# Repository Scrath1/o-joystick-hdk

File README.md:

# What is this?
This repository is a fork from olukelo's gimbal repository in which I uploaded his gimbal design converted to the .step format.
Furthermore this repository will hold my personal modifications on his gimbal as well as a modified version of [JFlyer81](https://www.thingiverse.com/jflyer81/designs) F-16 Grip and Hatswitches.
I have also uploaded some arduino code that I will use for my personal build of this combination. Schematics and a parts list may or may not follow.

## Bill of Materials
### Joystick:
**Electronics:**
- 4x [T 133A Push Buttons](./Datasheets/T-113A.pdf)
- 2x [4 directional hat switch](./Datasheets/SKQUCAA010-ALPS.pdf)
- 1x [RKJXT1F 4 directional stick switch with encoder](./Datasheets/rkjxt-1890304.pdf)
- 2x 6x6mm tactile push button
- 1x Seeeduino Xiao Microcontroller
- 3x [SN74HC165 PiSo Shift Register](./Datasheets/sn74hc165.pdf)
- 1x [RKJXV122400R ThumbStick](https://tech.alpsalpine.com/e/products/detail/RKJXV122400R/)
**Other:**
- 1x Spring 12mm long, 7mm diameter, 0.5mm filament diameter. Can be wider but should not be shorter or longer
- 1x Spring about 12mm long, 4mm diameter, 0.4mm filament diameter
- M4 Bolts and Nuts
- M3 Bolts and Nuts
- 2x M2 Bolts (M2x6 or M2x8) and Nuts
- 4x M3 Threaded Inserts (3x 6mm and 1x up to 10mm long)
- 2x Bearings MF 105 ZZ

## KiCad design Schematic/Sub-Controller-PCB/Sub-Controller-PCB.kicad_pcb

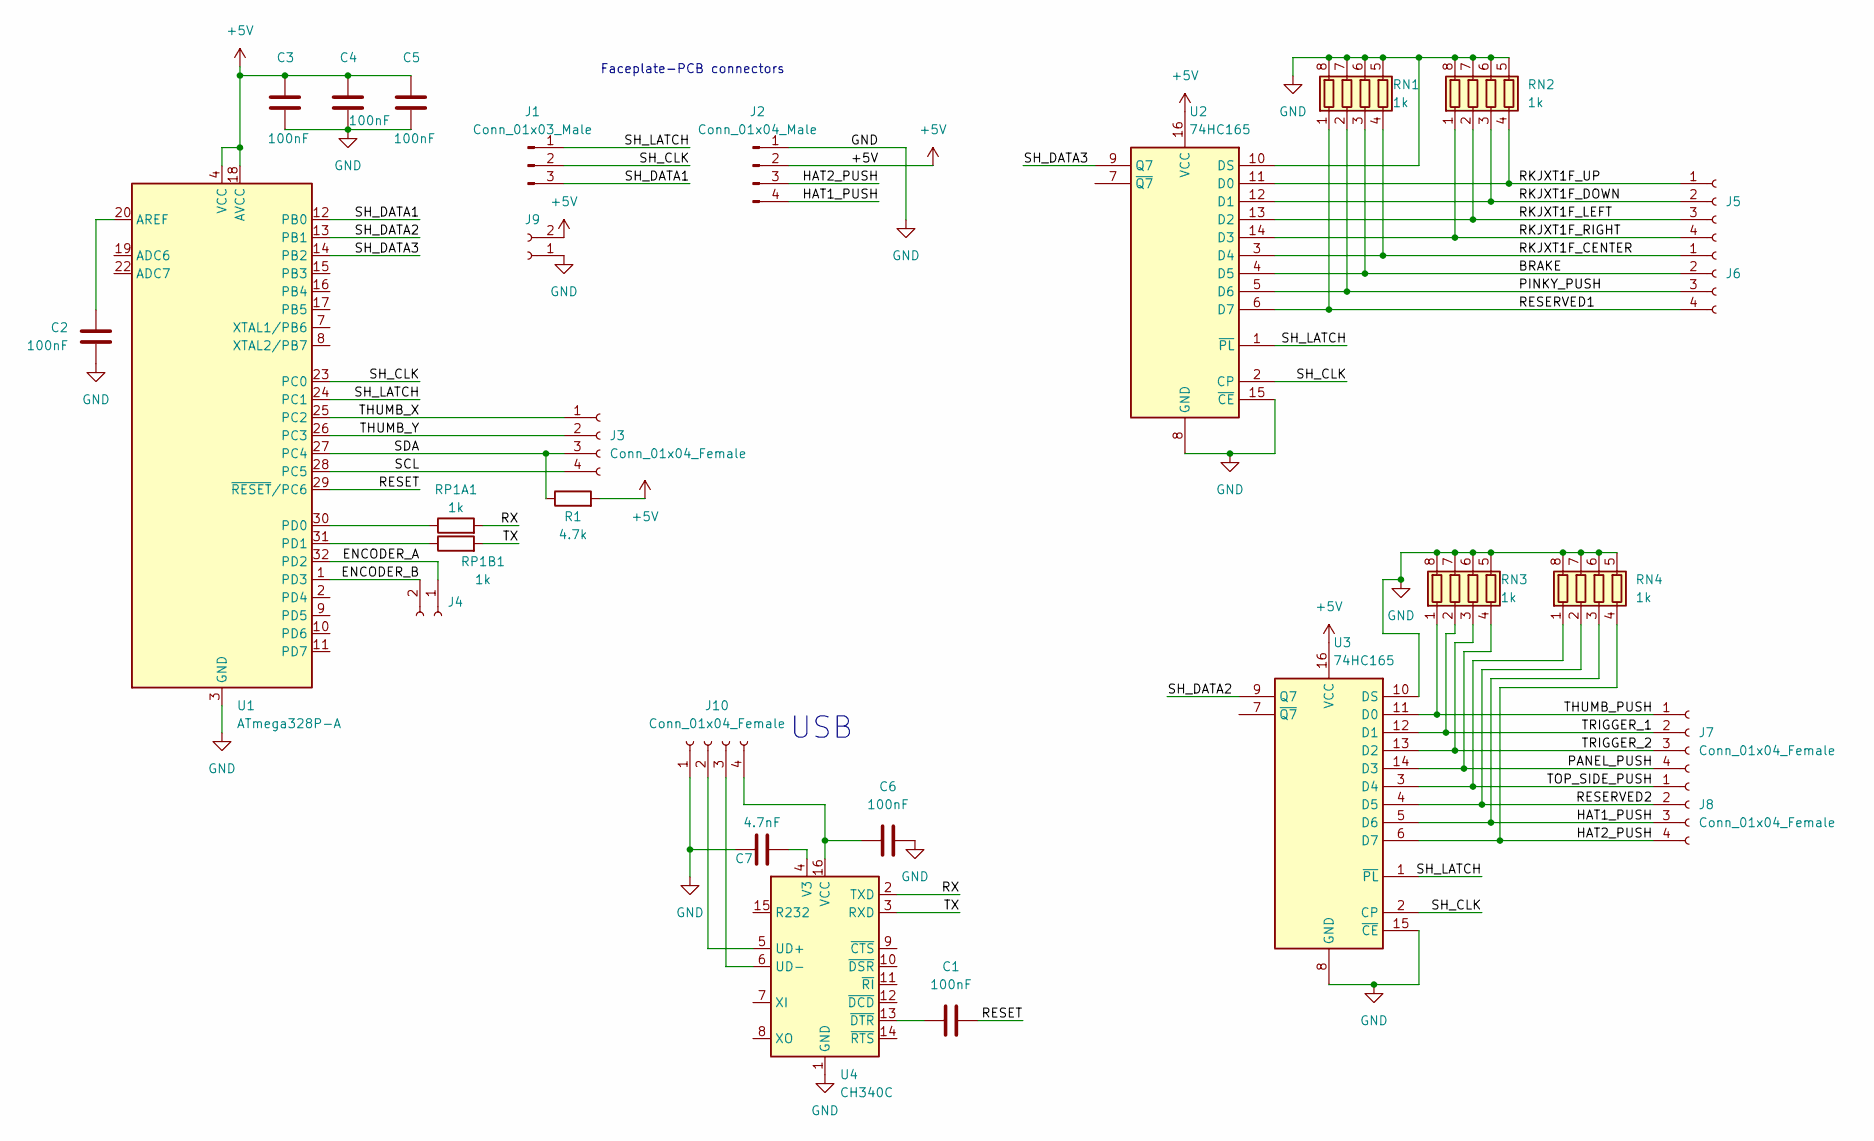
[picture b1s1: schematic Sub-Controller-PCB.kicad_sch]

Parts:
C1: 100nF; R_0603_1608Metric_Pad0.98x0.95mm_HandSolder
C2, C3, C4, C5, C6: 100nF; C_0603_1608Metric_Pad1.08x0.95mm_HandSolder
C7: 4.7nF; C_0603_1608Metric_Pad1.08x0.95mm_HandSolder
J1: Conn_01x03_Male; PinSocket_1x03_P2.54mm_Vertical
J2: Conn_01x04_Male; PinSocket_1x04_P2.54mm_Vertical
J3, J5, J6, J7, J8, J10: Conn_01x04_Female; PinSocket_1x04_P2.54mm_Vertical
J4, J9: Conn_01x02_Female; PinSocket_1x02_P2.54mm_Vertical
R1: 4.7k; R_0603_1608Metric_Pad0.98x0.95mm_HandSolder
RN1, RN2, RN3, RN4: 1k; R_Array_Convex_4x1206
RP1A1, RP1B1: 1k; R_0603_1608Metric_Pad0.98x0.95mm_HandSolder
U1: ATmega328P-A; TQFP-32_7x7mm_P0.8mm
U2, U3: 74HC165; TSSOP-16_4.4x5mm_P0.65mm
U4: CH340C; SOIC-16_3.9x9.9mm_P1.27mm

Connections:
+5V: C3.1, C4.1, C5.1, J2.2, J9.2, R1.2, U1.4 (VCC), U1.6 (VCC), U1.18 (AVCC), U2.16 (VCC), U3.16 (VCC)
/BRAKE: J6.2, RN1.3 (R3.1), U2.4 (D5)
/ENCODER_A: J4.1, U1.32 (PD2)
/ENCODER_B: J4.2, U1.1 (PD3)
/HAT1_PUSH: J2.4, J8.3, RN4.3 (R3.1), U3.5 (D6)
/HAT2_PUSH: J2.3, J8.4, RN4.4 (R4.1), U3.6 (D7)
/PANEL_PUSH: J7.4, RN3.4 (R4.1), U3.14 (D3)
/PINKY_PUSH: J6.3, RN1.2 (R2.1), U2.5 (D6)
/RESERVED1: J6.4, RN1.1 (R1.1), U2.6 (D7)
/RESERVED2: J8.2, RN4.2 (R2.1), U3.4 (D5)
/RESET: C1.2, U1.29 (~RESET/PC6)
/RKJXT1F_CENTER: J6.1, RN1.4 (R4.1), U2.3 (D4)
/RKJXT1F_DOWN: J5.2, RN2.3 (R3.1), U2.12 (D1)
/RKJXT1F_LEFT: J5.3, RN2.2 (R2.1), U2.13 (D2)
/RKJXT1F_RIGHT: J5.4, RN2.1 (R1.1), U2.14 (D3)
/RKJXT1F_UP: J5.1, RN2.4 (R4.1), U2.11 (D0)
/RX: RP1A1.2, U4.2 (TXD)
/SCL: J3.4, U1.28 (PC5)
/SDA: J3.3, R1.1, U1.27 (PC4)
/SH_CLK: J1.2, U1.23 (PC0), U2.2 (CP), U3.2 (CP)
/SH_DATA1: J1.3, U1.12 (PB0)
/SH_DATA2: U1.13 (PB1), U3.9 (Q7)
/SH_DATA3: U1.14 (PB2), U2.9 (Q7)
/SH_LATCH: J1.1, U1.24 (PC1), U2.1 (~PL), U3.1 (~PL)
/THUMB_PUSH: J7.1, RN3.1 (R1.1), U3.11 (D0)
/THUMB_X: J3.1, U1.25 (PC2)
/THUMB_Y: J3.2, U1.26 (PC3)
/TOP_SIDE_PUSH: J8.1, RN4.1 (R1.1), U3.3 (D4)
/TRIGGER_1: J7.2, RN3.2 (R2.1), U3.12 (D1)
/TRIGGER_2: J7.3, RN3.3 (R3.1), U3.13 (D2)
/TX: RP1B1.2, U4.3 (RXD)
GND: C2.2, C3.2, C4.2, C5.2, C6.2, C7.1, J2.1, J9.1, J10.1, RN1.5 (R4.2), RN1.6 (R3.2), RN1.7 (R2.2), RN1.8 (R1.2), RN2.5 (R4.2), RN2.6 (R3.2), RN2.7 (R2.2), RN2.8 (R1.2), RN3.5 (R4.2), RN3.6 (R3.2), RN3.7 (R2.2), RN3.8 (R1.2), RN4.5 (R4.2), RN4.6 (R3.2), RN4.7 (R2.2), RN4.8 (R1.2), U1.3 (GND), U1.5 (GND), U1.21 (GND), U2.8 (GND), U2.10 (DS), U2.15 (~CE), U3.8 (GND), U3.10 (DS), U3.15 (~CE), U4.1 (GND)
unnamed: C1.1, U4.13 (~DTR)
unnamed: C2.1, U1.20 (AREF)
unnamed: C6.1, J10.4, U4.16 (VCC)
unnamed: C7.2, U4.4 (V3)
unnamed: J10.2, U4.5 (UD+)
unnamed: J10.3, U4.6 (UD-)
unnamed: RP1A1.1, U1.30 (PD0)
unnamed: RP1B1.1, U1.31 (PD1)

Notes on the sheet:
USB
Faceplate-PCB connectors

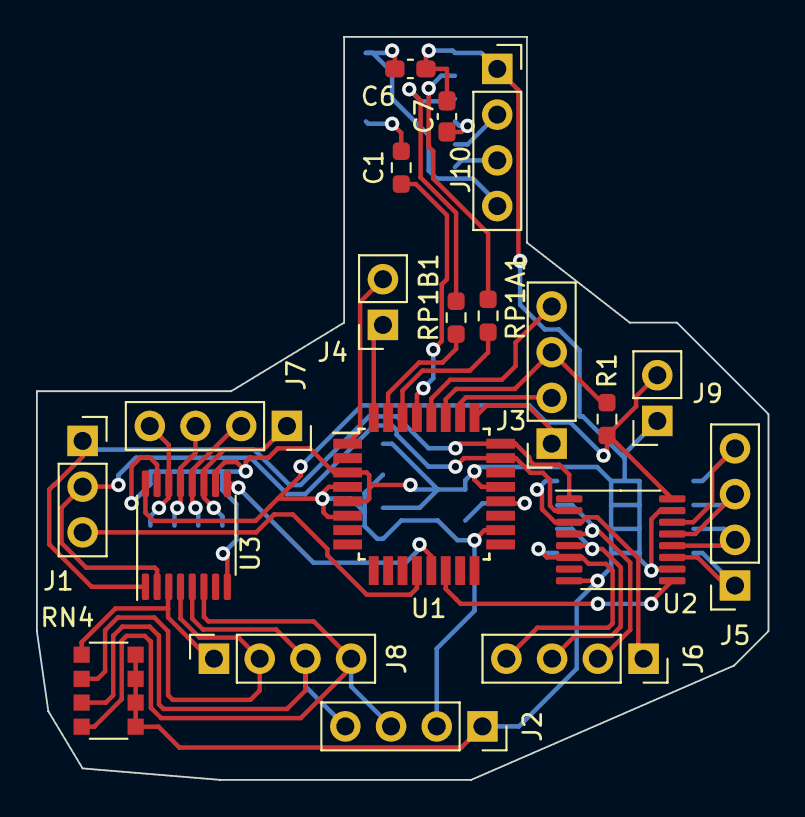
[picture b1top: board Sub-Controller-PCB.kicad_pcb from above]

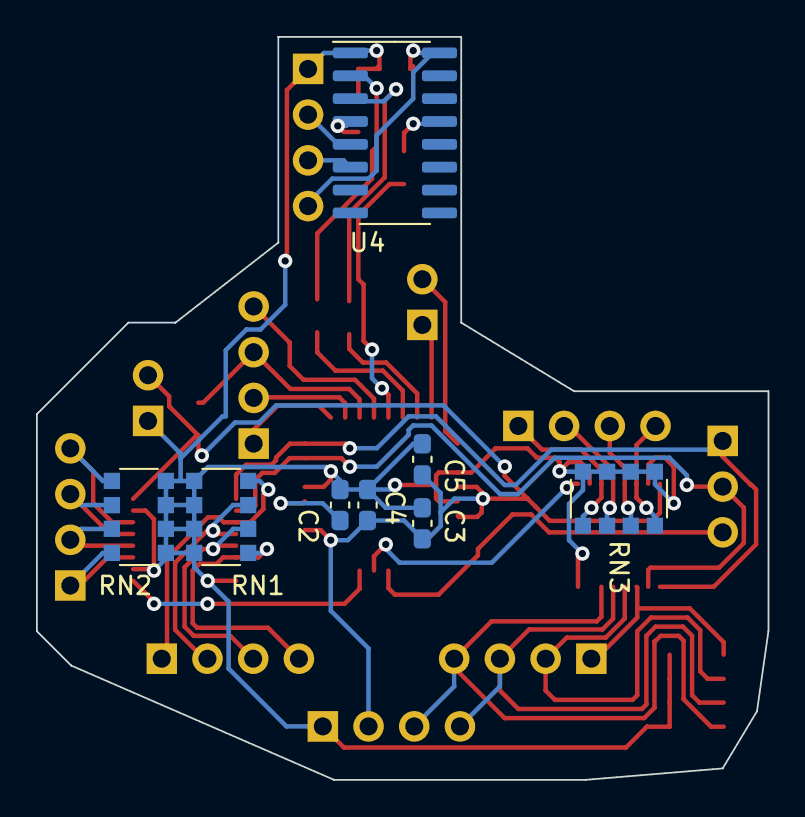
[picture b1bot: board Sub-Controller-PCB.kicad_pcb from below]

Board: 2 copper layers, 40.6 x 41.3 mm, 28 parts (8 on the bottom side), 40 nets.

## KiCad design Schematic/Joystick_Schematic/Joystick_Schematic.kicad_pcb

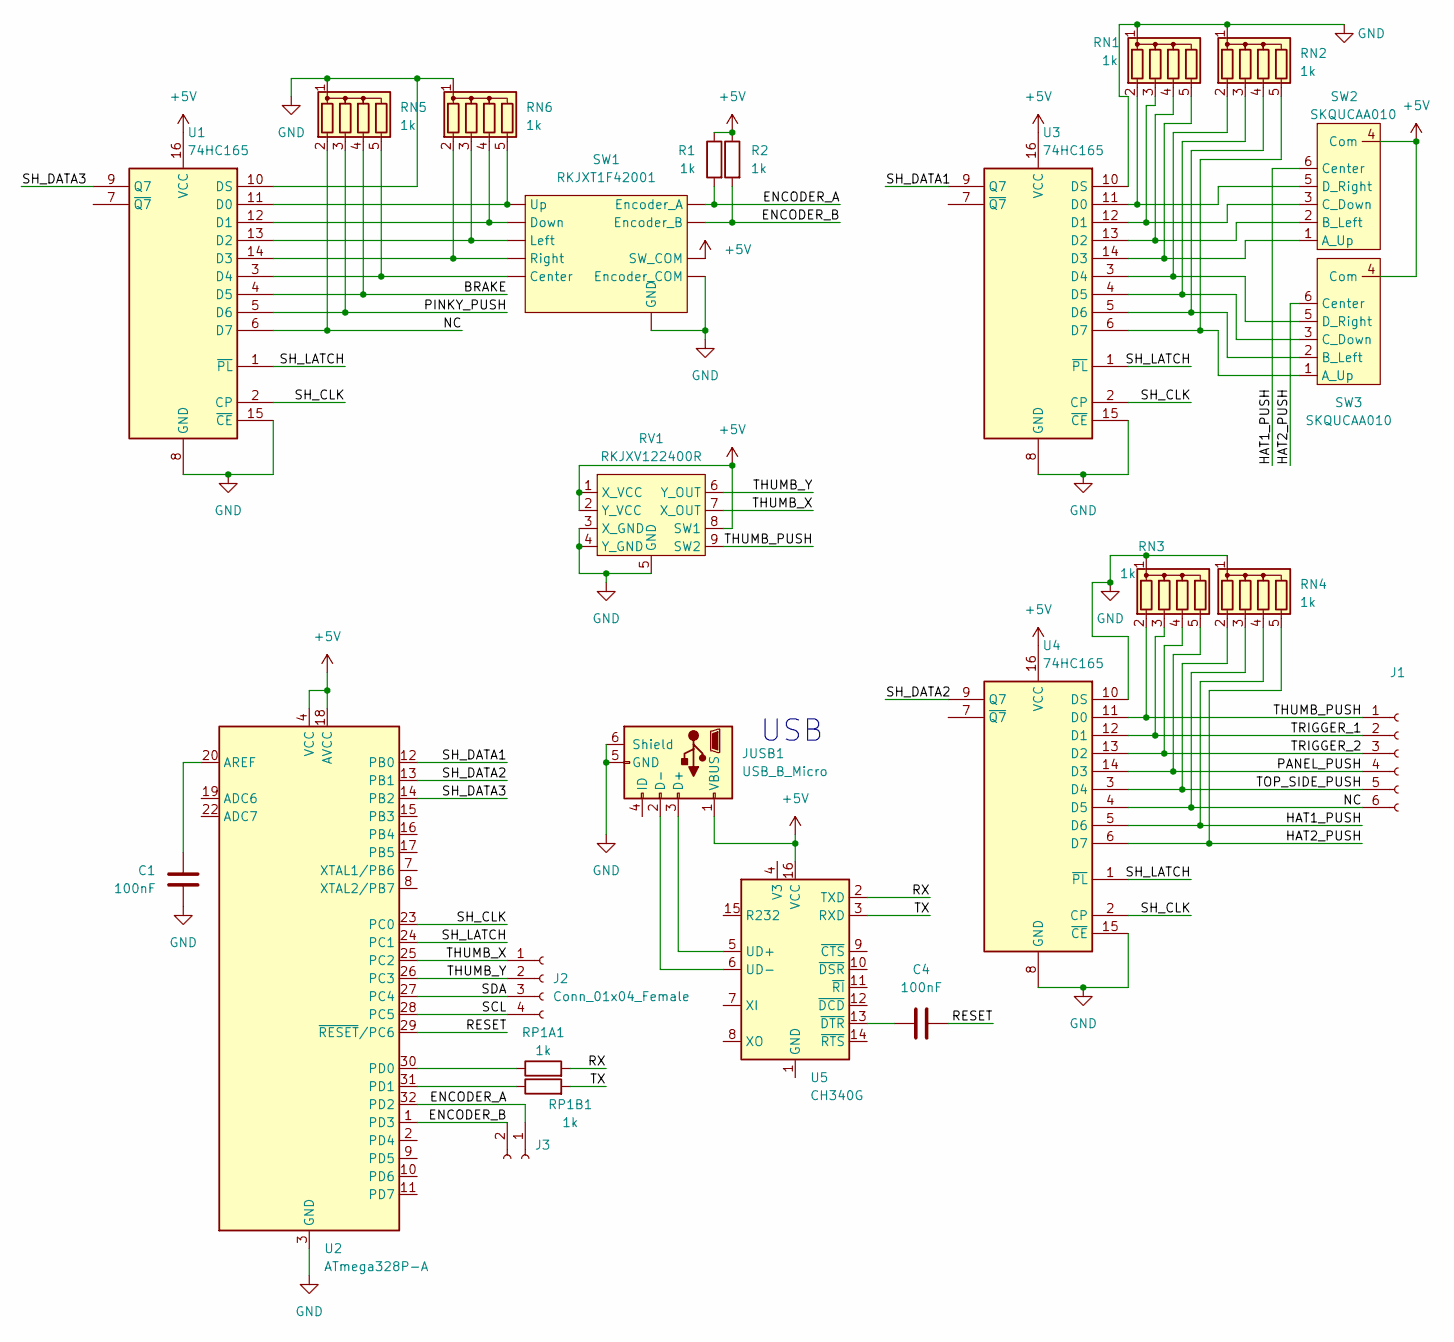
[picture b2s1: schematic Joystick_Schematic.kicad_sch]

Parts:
C1, C4: 100nF; R_0201_0603Metric_Pad0.64x0.40mm_HandSolder
J1: Conn_01x06_Female; PinSocket_1x06_P2.54mm_Vertical
J2: Conn_01x04_Female; PinSocket_1x04_P2.54mm_Vertical
J3: Conn_01x02_Female; PinSocket_1x02_P2.54mm_Vertical
JUSB1: USB_B_Micro; USB_Micro-B_Molex_47346-0001
R1, R2: 1k; R_0201_0603Metric_Pad0.64x0.40mm_HandSolder
RN1, RN2, RN3, RN4, RN5, RN6: 1k; R_Array_SIP5
RP1A1, RP1B1: 1k; R_0201_0603Metric_Pad0.64x0.40mm_HandSolder
RV1: RKJXV122400R
SW1: RKJXT1F42001
SW2, SW3: SKQUCAA010
U1, U3, U4: 74HC165; TSSOP-16_4.4x5mm_P0.65mm
U2: ATmega328P-A; TQFP-32_7x7mm_P0.8mm
U5: CH340G; SOIC-16_3.9x9.9mm_P1.27mm

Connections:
+5V: JUSB1.1 (VBUS), R1.1, R2.1, RV1.1 (X_VCC), RV1.2 (Y_VCC), RV1.8 (SW1), SW1., SW2.4 (Com), SW3.4 (Com), U1.16 (VCC), U2.4 (VCC), U2.6 (VCC), U2.18 (AVCC), U3.16 (VCC), U4.16 (VCC), U5.16 (VCC)
/BRAKE: RN5.4 (R3), U1.4 (D5)
/ENCODER_A: J3.1, R1.2, SW1., U2.32 (PD2)
/ENCODER_B: J3.2, R2.2, SW1., U2.1 (PD3)
/HAT1_PUSH: RN4.4 (R3), SW2.6 (Center), U4.5 (D6)
/HAT2_PUSH: RN4.5 (R4), SW3.6 (Center), U4.6 (D7)
/NC: J1.6, RN4.3 (R2), RN5.2 (R1), U1.6 (D7), U4.4 (D5)
/PANEL_PUSH: J1.4, RN3.5 (R4), U4.14 (D3)
/PINKY_PUSH: RN5.3 (R2), U1.5 (D6)
/RESET: C4.2, U2.29 (~RESET/PC6)
/RX: RP1A1.2, U5.2 (TXD)
/SCL: J2.4, U2.28 (PC5)
/SDA: J2.3, U2.27 (PC4)
/SH_CLK: U1.2 (CP), U2.23 (PC0), U3.2 (CP), U4.2 (CP)
/SH_DATA1: U2.12 (PB0), U3.9 (Q7)
/SH_DATA2: U2.13 (PB1), U4.9 (Q7)
/SH_DATA3: U1.9 (Q7), U2.14 (PB2)
/SH_LATCH: U1.1 (~PL), U2.24 (PC1), U3.1 (~PL), U4.1 (~PL)
/THUMB_PUSH: J1.1, RN3.2 (R1), RV1.9 (SW2), U4.11 (D0)
/THUMB_X: J2.1, RV1.7 (X_OUT), U2.25 (PC2)
/THUMB_Y: J2.2, RV1.6 (Y_OUT), U2.26 (PC3)
/TOP_SIDE_PUSH: J1.5, RN4.2 (R1), U4.3 (D4)
/TRIGGER_1: J1.2, RN3.3 (R2), U4.12 (D1)
/TRIGGER_2: J1.3, RN3.4 (R3), U4.13 (D2)
/TX: RP1B1.2, U5.3 (RXD)
GND: C1.2, JUSB1.5 (GND), JUSB1.6 (Shield), RN1.1 (common), RN2.1 (common), RN3.1 (common), RN4.1 (common), RN5.1 (common), RN6.1 (common), RV1.3 (X_GND), RV1.4 (Y_GND), RV1.5 (GND), SW1., U1.8 (GND), U1.10 (DS), U1.15 (~CE), U2.3 (GND), U2.5 (GND), U2.21 (GND), U3.8 (GND), U3.10 (DS), U3.15 (~CE), U4.8 (GND), U4.10 (DS), U4.15 (~CE)
unnamed: C1.1, U2.20 (AREF)
unnamed: C4.1, U5.13 (~DTR)
unnamed: JUSB1.2 (D-), U5.6 (UD-)
unnamed: JUSB1.3 (D+), U5.5 (UD+)
unnamed: RP1A1.1, U2.30 (PD0)
unnamed: RP1B1.1, U2.31 (PD1)
unnamed: RN6.5 (R4), SW1., U1.11 (D0)
unnamed: RN5.5 (R4), SW1., U1.3 (D4)
unnamed: RN6.4 (R3), SW1., U1.12 (D1)
unnamed: RN6.3 (R2), SW1., U1.13 (D2)
unnamed: RN6.2 (R1), SW1., U1.14 (D3)
unnamed: RN1.5 (R4), SW2.1 (A_Up), U3.14 (D3)
unnamed: RN1.4 (R3), SW2.2 (B_Left), U3.13 (D2)
unnamed: RN1.3 (R2), SW2.3 (C_Down), U3.12 (D1)
unnamed: RN1.2 (R1), SW2.5 (D_Right), U3.11 (D0)
unnamed: RN2.5 (R4), SW3.1 (A_Up), U3.6 (D7)
unnamed: RN2.4 (R3), SW3.2 (B_Left), U3.5 (D6)
unnamed: RN2.3 (R2), SW3.3 (C_Down), U3.4 (D5)
unnamed: RN2.2 (R1), SW3.5 (D_Right), U3.3 (D4)

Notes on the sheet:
USB

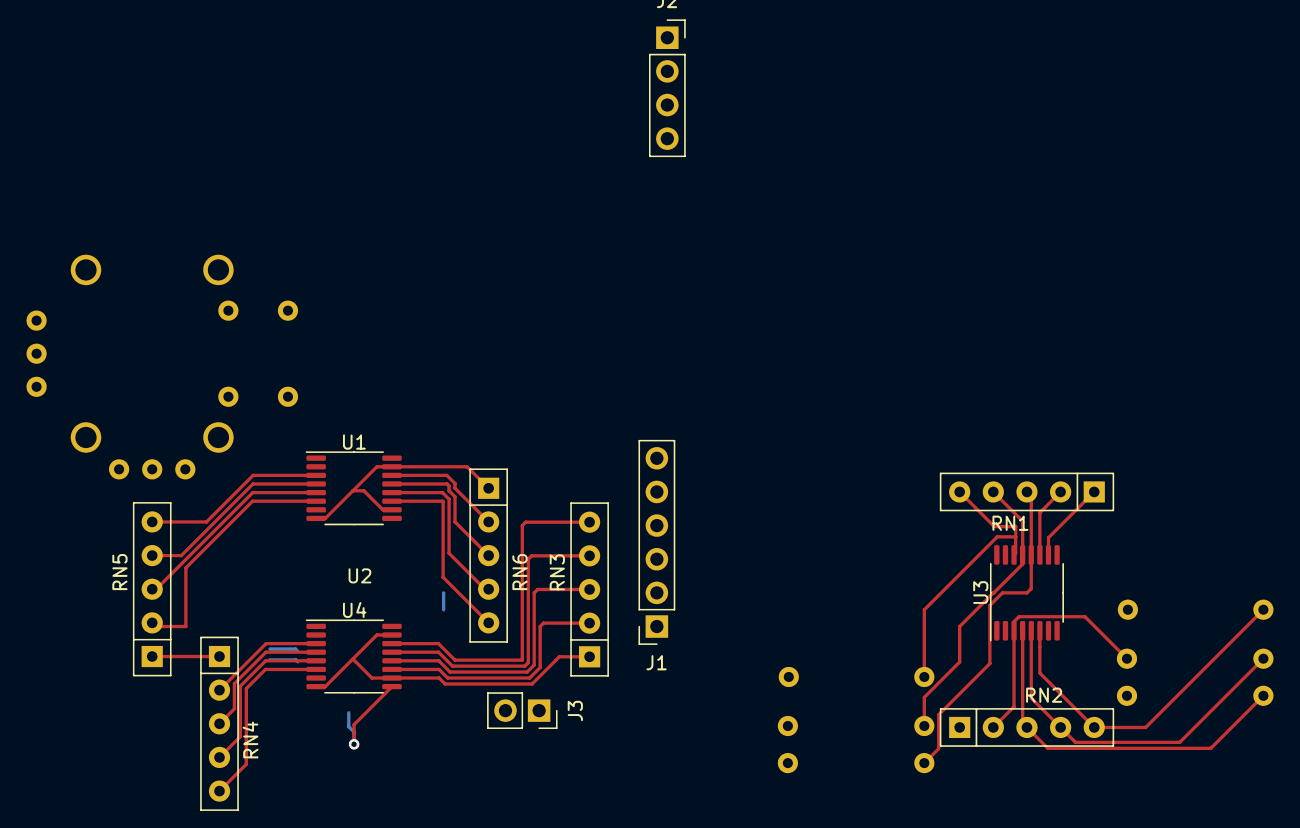
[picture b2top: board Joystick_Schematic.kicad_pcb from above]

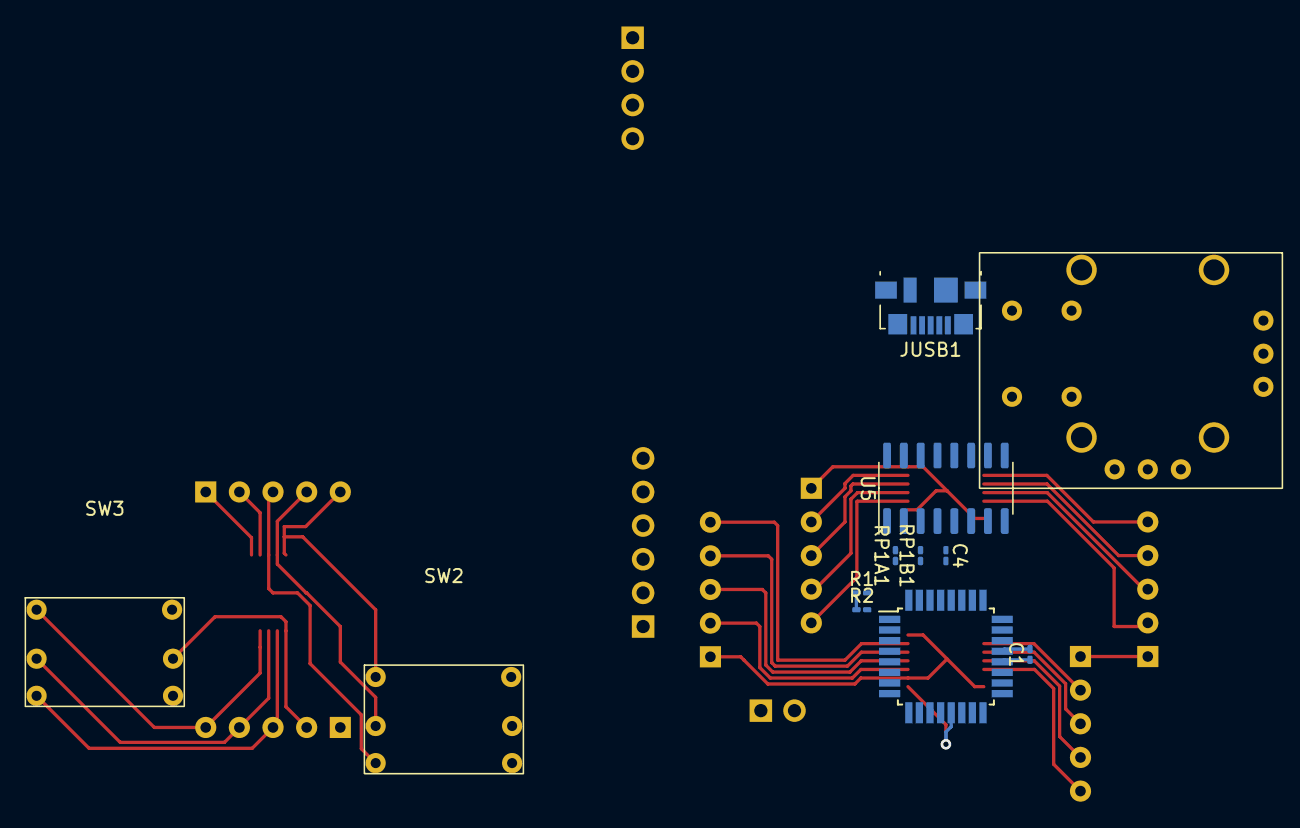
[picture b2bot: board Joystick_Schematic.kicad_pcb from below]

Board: 2 copper layers, 24 parts (12 on the bottom side), 45 nets.

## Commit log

2021-04-06 Added step file
2021-04-06 fixed some issue with the original step file and included the housing in the file
2021-05-12 added readme and step file of modified design
2021-05-12 added code which (theoretically) implements i2c communication for the 2 arduinos
2021-05-12 fixed i2c data transmission
2021-07-19 removed old stuff from slave code
2021-07-19 joystick buttons working
2021-07-19 joystick axis working
2021-07-21 finalised joystick design
2021-07-21 added axis state println
2021-07-21 added thumbstick and axis calibration
2021-07-25 bugfix for center calibration and adjusted calibration values
2021-10-28 some stuff
2022-10-15 Started rebuild
2022-10-15 removed out of date files and created prove of concept piso code
2022-10-20 continued schematic
2022-10-28 Schematic update
2022-10-30 Schematic update again and started PCB
2022-11-02 Finished Faceplate-PCB
2022-11-02 started working on Sub-Controller-PCB
2022-11-03 Finished preliminary routing of sub-controller pcb
2022-11-03 small modifications to to sub-controller-pcb
2023-01-07 schematic changes. Bypass capacitor, I2C pullup
2023-01-24 PCB rework
2023-11-15 Some PCB changes
